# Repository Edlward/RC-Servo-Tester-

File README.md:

# RC-Servo-Tester-
DIY RC Servo Tester (STM32F0 &amp; LABVIEW GUI)

http://www.mylv.net/opensource/opensource_view.aspx?BID=96435

<object width="845" height="510">
<iframe width="1280" height="720" src="https://www.youtube.com/embed/h2mnOkbDfCk" frameborder="0" allowfullscreen></iframe>
</object>

http://youtu.be/h2mnOkbDfCk

집어넣은 기능은 아래와 같습니다.
 1. DIGITAL SERVO MODE  지원(4ms 주기) : 
 주로 쿼드 콥터용 변속기에서 빠른 응답성이 필요해서 순정 변속기를 DIGITAL SERVO MODE 펌웨어로 펍업해서 쓰거나 전용 DIGITAL SERVO MODE로 빠른 펄스 속도를 지원하는 변속기를 구매해서 쓰고있죠.
  볼륨을 최소로 놓고 PUSH BUTTON을 2초이상 누르면 LED3개가 동시에 4번 깜빡이고 DIGITAL SERVO MODE 로 변경됩니다.
   일반 PPM MODE(20ms 펄스주기)로 변경할때에는 볼륨을 최대로 놓고 PUSH BUTTON을 2초이상 누르면 LED가 좌->우->좌 3번 왔다갔다 점멸 하면서 PPM MODE로 변경됩니다.

 2. 서보 테스터 최대 최소 범위 가변 기능 :
볼륨을 중심에 놓고(중심에 볼륨을 놓으면 메뉴얼 모드에서 3개의 LED가 모두 점등되면 중심입니다.) PUSH BUTTON을 2초이상 길게 누르면 PPPM 출력펄스가 최대 최소 값이 변경됩니다.
표준 상태에서는 1.0ms ~ 2.0ms의 HIGH WIDTH PULSE 출력되며, 넓은범위 상태에서는 0.8ms ~ 2.2ms의 펄스 HIGH WIDTH PULSE가 출력되게 됩니다.
3. 가변 자동모드 :
PUSH 버튼을 잛게 누르면 수동제어->중심고정->자동모드 로 동작 모드로 변경됩니다.
자동모드로 설정될경우 맨 우측 LED가 점등되며, 자동모드 상태에서 볼륨을 돌려주면 자동모드로 움직이는 속도가 가변됩니다. (자동모드는 서보테스터에서 최소 PPM PULSE 에서 최대 PPM PULSE가 까지 오르락 내리락 하면서 신호가 출력됩니다.)
턴니지 서보테스터에는 자동 모드는 한가지 속도로 고정되죠
.
4. 출력되는 PPM PULSE의 포지션을 알려주는 LED기능
 넓은 범위 출력으로 서보테스터를 셋팅해서 사용시 PPM PULSE가 1.0ms 포지보다 낮아지면 맨 좌측 LED의 밝기가 어두어 집니다. 반대로 2.0ms 보다 크면 맨 우측 LED가 어두워 지고 중앙(1.498~1.502ms)에 위치할경우 3개의 모든 LED가 들어오게 됩니다.
LED 밝기와 점등 갯수를 보고 서보테스터에서 출력되는 펄스가 1.0인지 2.0인지 중심인지 알수있도록 하였습니다.

5. 원격제어 기능
USB-UART와 서보테스터의 INPUT 핀을 RXD, TXD와 연결하면 PC의 GUI 프로그램에서 서보테스터를 원격으로 제어 가능합니다. GUI프로그램은 LABVIEW로 만들었으며 첨부된 파일에 만들어진 실행 파일 및 소스가 있습니다.

DIGITAL SERVO MODE 와 STANDARD SERVO(ANALOG SERVO) PPM MODE를 변화하는 동영상 입니다.
아날로그 서보라서 DIGITAL SERVO MODE 를 지원 못해서 변경시 웅웅거리는 잡음이 서보에서 나게 됩니다.
이렇게 오래 쓰면 써보 망가집니다. --;
볼륨을 최대로 놓고 푸쉬버튼을 2초이상 눌주면 표준 PPM MODE이고 볼륨을 최소로 놓고 푸쉬버튼을 2초이상 누르면 DIGITAL SERVO MODE로 변경됩니다.

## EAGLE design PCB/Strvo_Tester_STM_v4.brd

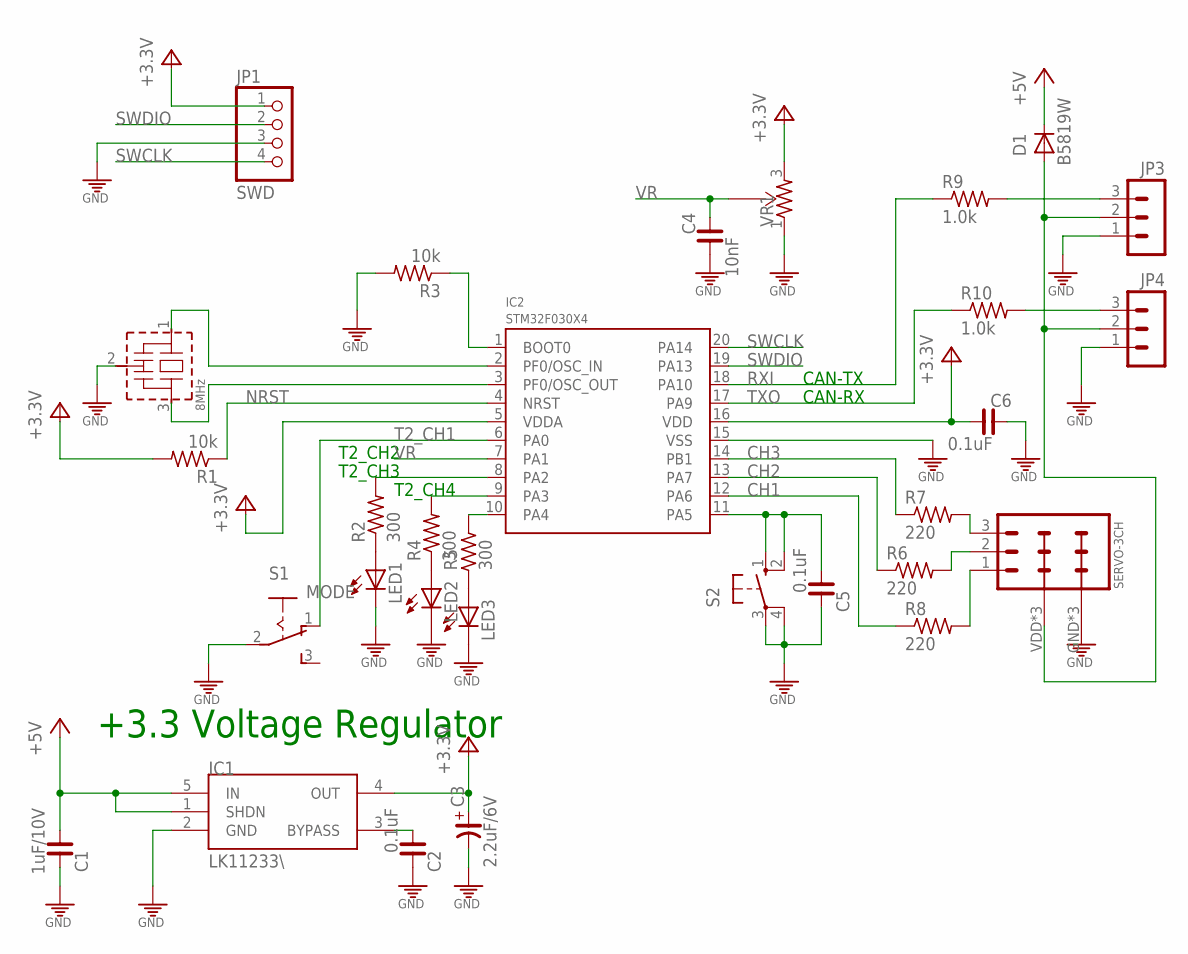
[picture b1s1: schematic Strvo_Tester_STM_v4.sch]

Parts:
C1: 1uF/10V; C0603
C2, C5, C6: 0.1uF; C0603
C3: 2.2uF/6V; C2012/T
C4: 10nF; C0603
D1: B5819W; SOD323
IC1: LK11233\; SOT23-5L
IC2: STM32F030X4; TSSOP20
JP1: SWD; 1X04M
JP2: SERVO-3CH; SERVO-3CH1
JP3, JP4: MA03-1SMALL; MA03-1-S
LED1, LED2, LED3: LED3MM
Q1: 8MHz; CSTLA_X
R1, R3: 10k; R0603
R2, R4, R5: 300; R0603
R6, R7, R8: 220; R0603
R9, R10: 1.0k; R0603
S1: MODE; 255SB
S2: 10-XX; B3F-10XX
VR1: R-TRIMMER-SMDPTV; PTV09

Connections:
3V3: C3.+, C6.2, IC1.4 (OUT), IC2.5 (VDDA), IC2.16 (VDD), JP1.1, R1.2, VR1.3
+5V: C1.2, D1.C, IC1.1 (SHDN), IC1.5 (IN)
CH1: IC2.12 (PA6), R8.1
CH2: IC2.13 (PA7), R6.1
CH3: IC2.14 (PB1), R7.1
GND: C1.1, C2.1, C3.-, C4.2, C5.1, C6.1, IC1.2 (GND), IC2.15 (VSS), JP1.3, JP2.GND, JP2.GND@1 (GND), JP2.GND@2 (GND), JP3.1, JP4.1, LED1.K (C), LED2.K (C), LED3.K (C), Q1.2 (GND), R3.2, S1.2, S2.3, S2.4 (P1), VR1.1
unnamed: LED1.A, R2.1
unnamed: IC2.2 (PF0/OSC_IN), Q1.1 (IN)
unnamed: IC2.3 (PF0/OSC_OUT), Q1.3 (OUT)
unnamed: JP2.3, R7.2
unnamed: IC2.8 (PA2), R2.2
unnamed: IC2.1 (BOOT0), R3.1
unnamed: C5.2, IC2.11 (PA5), S2.1 (S), S2.2 (S1)
unnamed: C2.2, IC1.3 (BYPASS)
unnamed: JP2.2, R6.2
unnamed: IC2.10 (PA4), R5.2
unnamed: LED2.A, R4.1
unnamed: JP2.1, R8.2
unnamed: IC2.9 (PA3), R4.2
unnamed: JP3.3, R9.2
unnamed: JP4.3, R10.2
unnamed: LED3.A, R5.1
unnamed: D1.A, JP2.VDD (+5V), JP2.VDD@1 (+5V), JP2.VDD@2 (+5V), JP3.2, JP4.2
NRST: IC2.4 (NRST), R1.1
RXI: IC2.18 (PA10), R9.1
SWCLK: IC2.20 (PA14), JP1.4
SWDIO: IC2.19 (PA13), JP1.2
T2_CH1: IC2.6 (PA0), S1.1 (O)
TXO: IC2.17 (PA9), R10.1
VR: C4.1, IC2.7 (PA1), VR1.2

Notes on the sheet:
+3.3 Voltage Regulator
T2_CH2
T2_CH3
T2_CH4
CAN-TX
CAN-RX

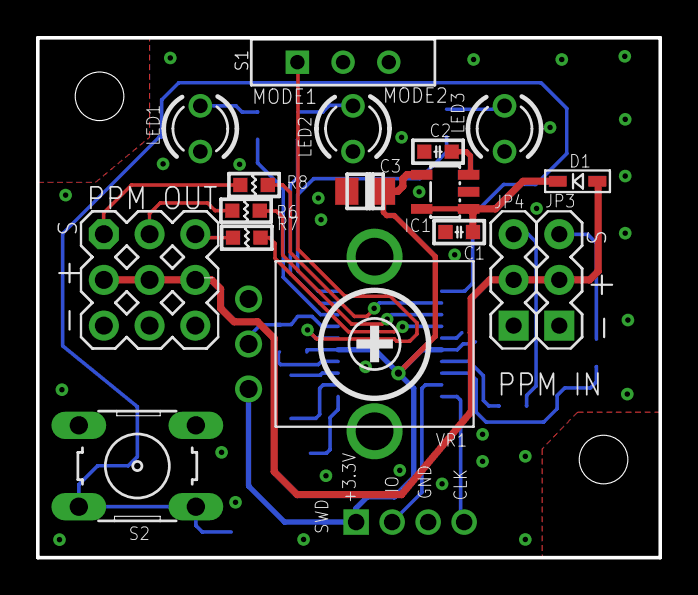
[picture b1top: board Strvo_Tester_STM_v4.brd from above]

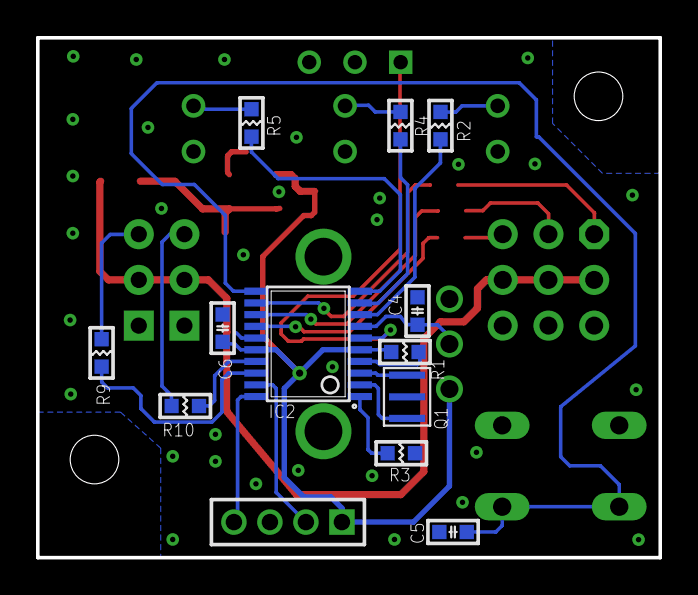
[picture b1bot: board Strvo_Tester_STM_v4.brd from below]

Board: 2 copper layers, 34.6 x 28.9 mm, 30 parts (13 on the bottom side), 30 nets.
